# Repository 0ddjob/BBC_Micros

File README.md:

# BBC Micros
 Projects for the BBC Model A/B and Master.

## [Master Compact Floppy Interface](/Master_Compact_FDC_Interface)
Simple adaptor board to convert the DB25 floppy interface to a standard IDC 34-way header.
### Status: TESTED
- 17-Nov-2024: test PCBs ordered from PCBWAY
- 20-Nov-2024: PCBs shipped
- 27-Nov-2024: PCBs arrived
- 3-Dec-2024: tested successfully
<br>

```
DB25             34-IDC
                  2  1
        /INUSE    4--3 
                  6  5
    1---INDEX-----8  7
14  2---/DS0-----10  9
15  3---/DS1-----12 11
16  4---/DS2-----14 13
17  5---/MOTOR---16 15
18  6---/DIR-----18 17
19  7---/SEEK----20 19
20  8---/DATA----22 21
21  9---/ENABLE--24 23
22 10---/TRK0----26 25
23 11---/WRPROT--28 27
24 12---/READ----30 29
25 13---/SIDE----32 31
                 34 33

Pins 14-25 on DB25 connected to GND.
Odd pins on IDC connected to GND.
The Master Compact's original floppy cable has IDC pins 3 & 4 connected,
i.e. /INUSE grounded.  This doesn't seem to matter when using the Gotek.
```

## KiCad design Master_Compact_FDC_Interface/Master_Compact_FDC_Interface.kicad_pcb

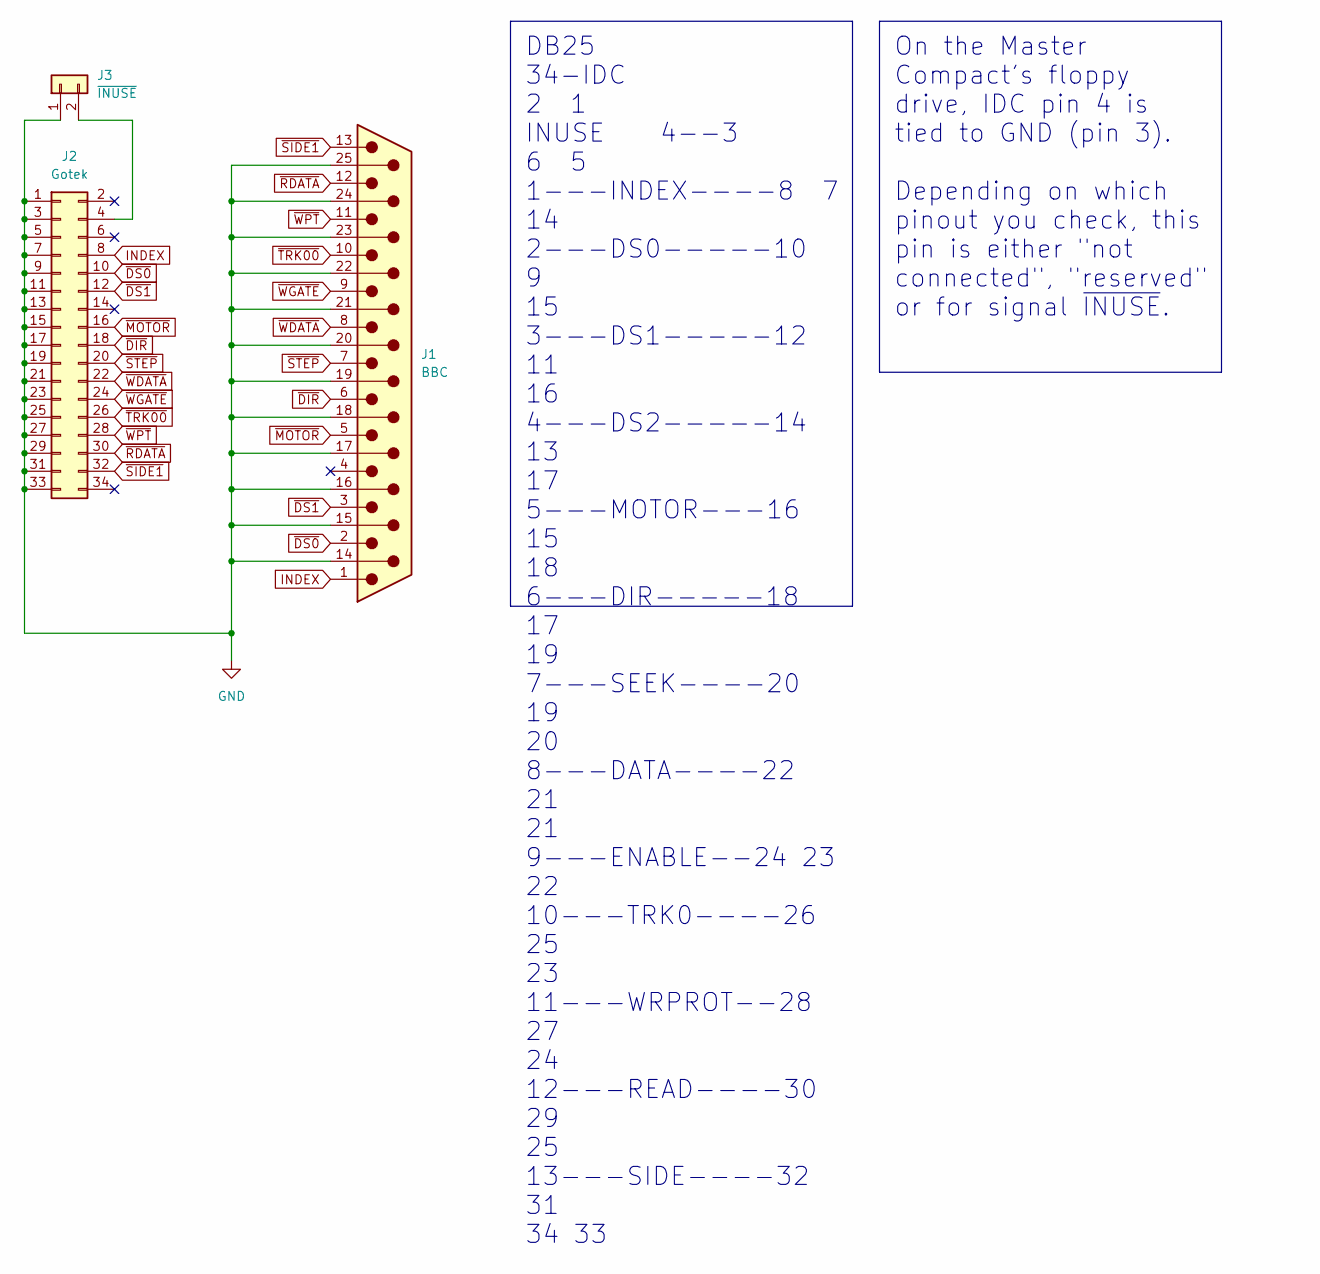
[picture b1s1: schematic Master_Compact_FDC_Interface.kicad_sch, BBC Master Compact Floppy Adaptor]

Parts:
J1: BBC; DSUB-25_Male_EdgeMount_P2.77mm
J2: Gotek; PinHeader_2x17_P2.54mm_Vertical
J3: ~{INUSE}; PinHeader_1x02_P2.54mm_Vertical

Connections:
GND: J1.14, J1.15, J1.16, J1.17, J1.18, J1.19, J1.20, J1.21, J1.22, J1.23, J1.24, J1.25, J2.1, J2.3, J2.5, J2.7, J2.9, J2.11, J2.13, J2.15, J2.17, J2.19, J2.21, J2.23, J2.25, J2.27, J2.29, J2.31, J2.33, J3.1
INDEX: J1.1, J2.8
unnamed: J2.4, J3.2
~DIR: J1.6, J2.18
~DS0: J1.2, J2.10
~DS1: J1.3, J2.12
~MOTOR: J1.5, J2.16
~RDATA: J1.12, J2.30
~SIDE1: J1.13, J2.32
~STEP: J1.7, J2.20
~TRK00: J1.10, J2.26
~WDATA: J1.8, J2.22
~WGATE: J1.9, J2.24
~WPT: J1.11, J2.28

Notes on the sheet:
On the Master Compact's floppy drive, IDC pin 4 is tied to GND (pin 3). Depending on which pinout you check, this pin is either "not connected", "reserved" or for signal ~{INUSE}.
DB25 34-IDC 2 1 INUSE 4--3 6 5 1---INDEX----8 7 14 2---DS0-----10 9 15 3---DS1-----12 11 16 4---DS2-----14 13 17 5---MOTOR---16 15 18 6---DIR-----18 17 19 7---SEEK----20 19 20 8---DATA----22 21 21 9---ENABLE--24 23 22 10---TRK0----26 25 23 11---WRPROT--28 27 24 12---READ----30 29 25 13---SIDE----32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

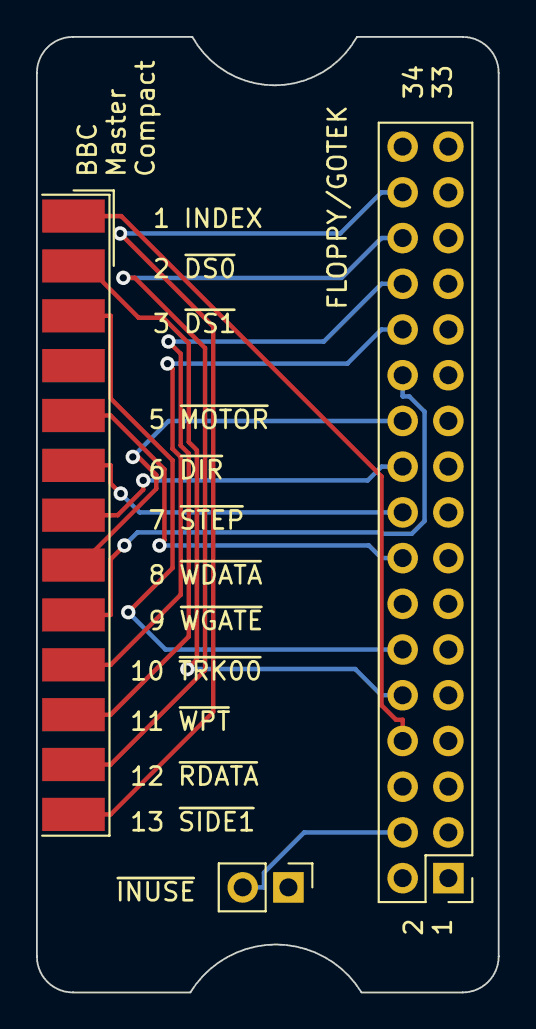
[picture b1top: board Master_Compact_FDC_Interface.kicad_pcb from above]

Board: 2 copper layers, 25.7 x 53.1 mm, 3 parts (0 on the bottom side), 14 nets.

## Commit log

2024-11-16 Initial
2024-11-16 Renamed Gerbers file
2024-11-16 3D render
2024-11-17 Reversed IDC header
2024-12-02 Added "schematic scraps" section
2024-12-03 Added Gotek ADFS files
2025-02-15 Added built pictures
